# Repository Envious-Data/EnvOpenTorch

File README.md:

# EnvOpenTorch
 A open source rechargable LED Torch

## Notes
This design is a bit jank and can certaily do with some improvement, If you feel like doing that then please do so and make a PR.

Generally speaking is to have a decently powerful open source LED torch, Im hoping for 10K lumens and some basic brightness control, anything else is bonnus features but there are some i'd like such as PD charging and being able to act as a battery bank if needed.

## Future plans
Im probably going to sell this as a full unit or kit other than the need to supply your own cells, I havent decided on 3S2P or 6S1P but for the time being the charge circuit can handle upto 4S.

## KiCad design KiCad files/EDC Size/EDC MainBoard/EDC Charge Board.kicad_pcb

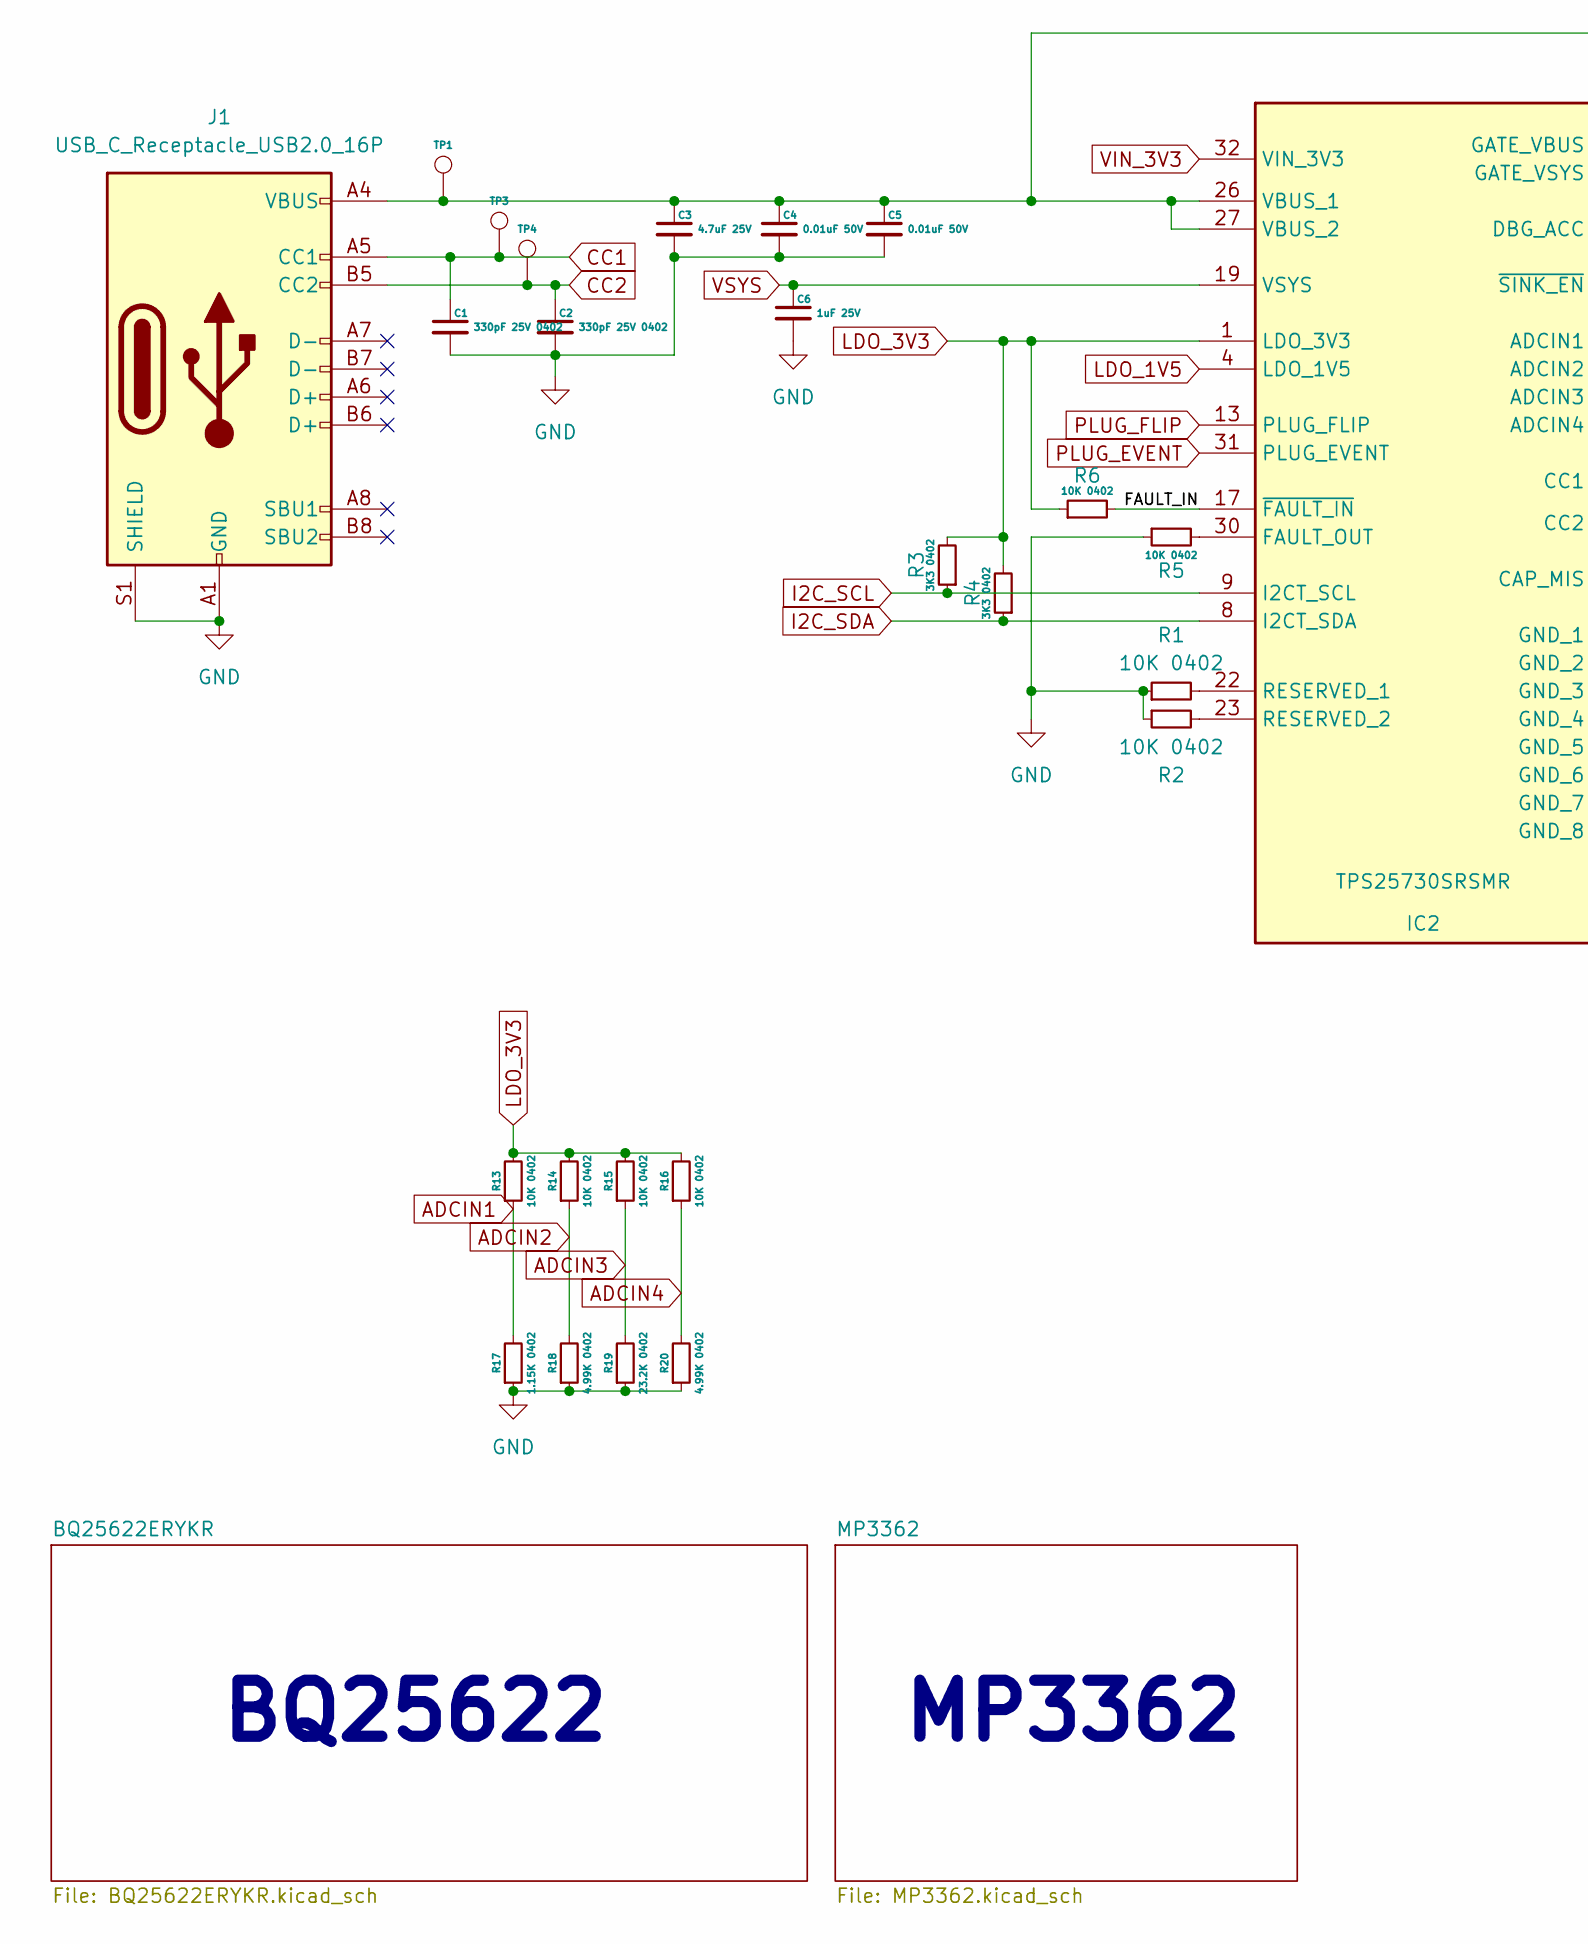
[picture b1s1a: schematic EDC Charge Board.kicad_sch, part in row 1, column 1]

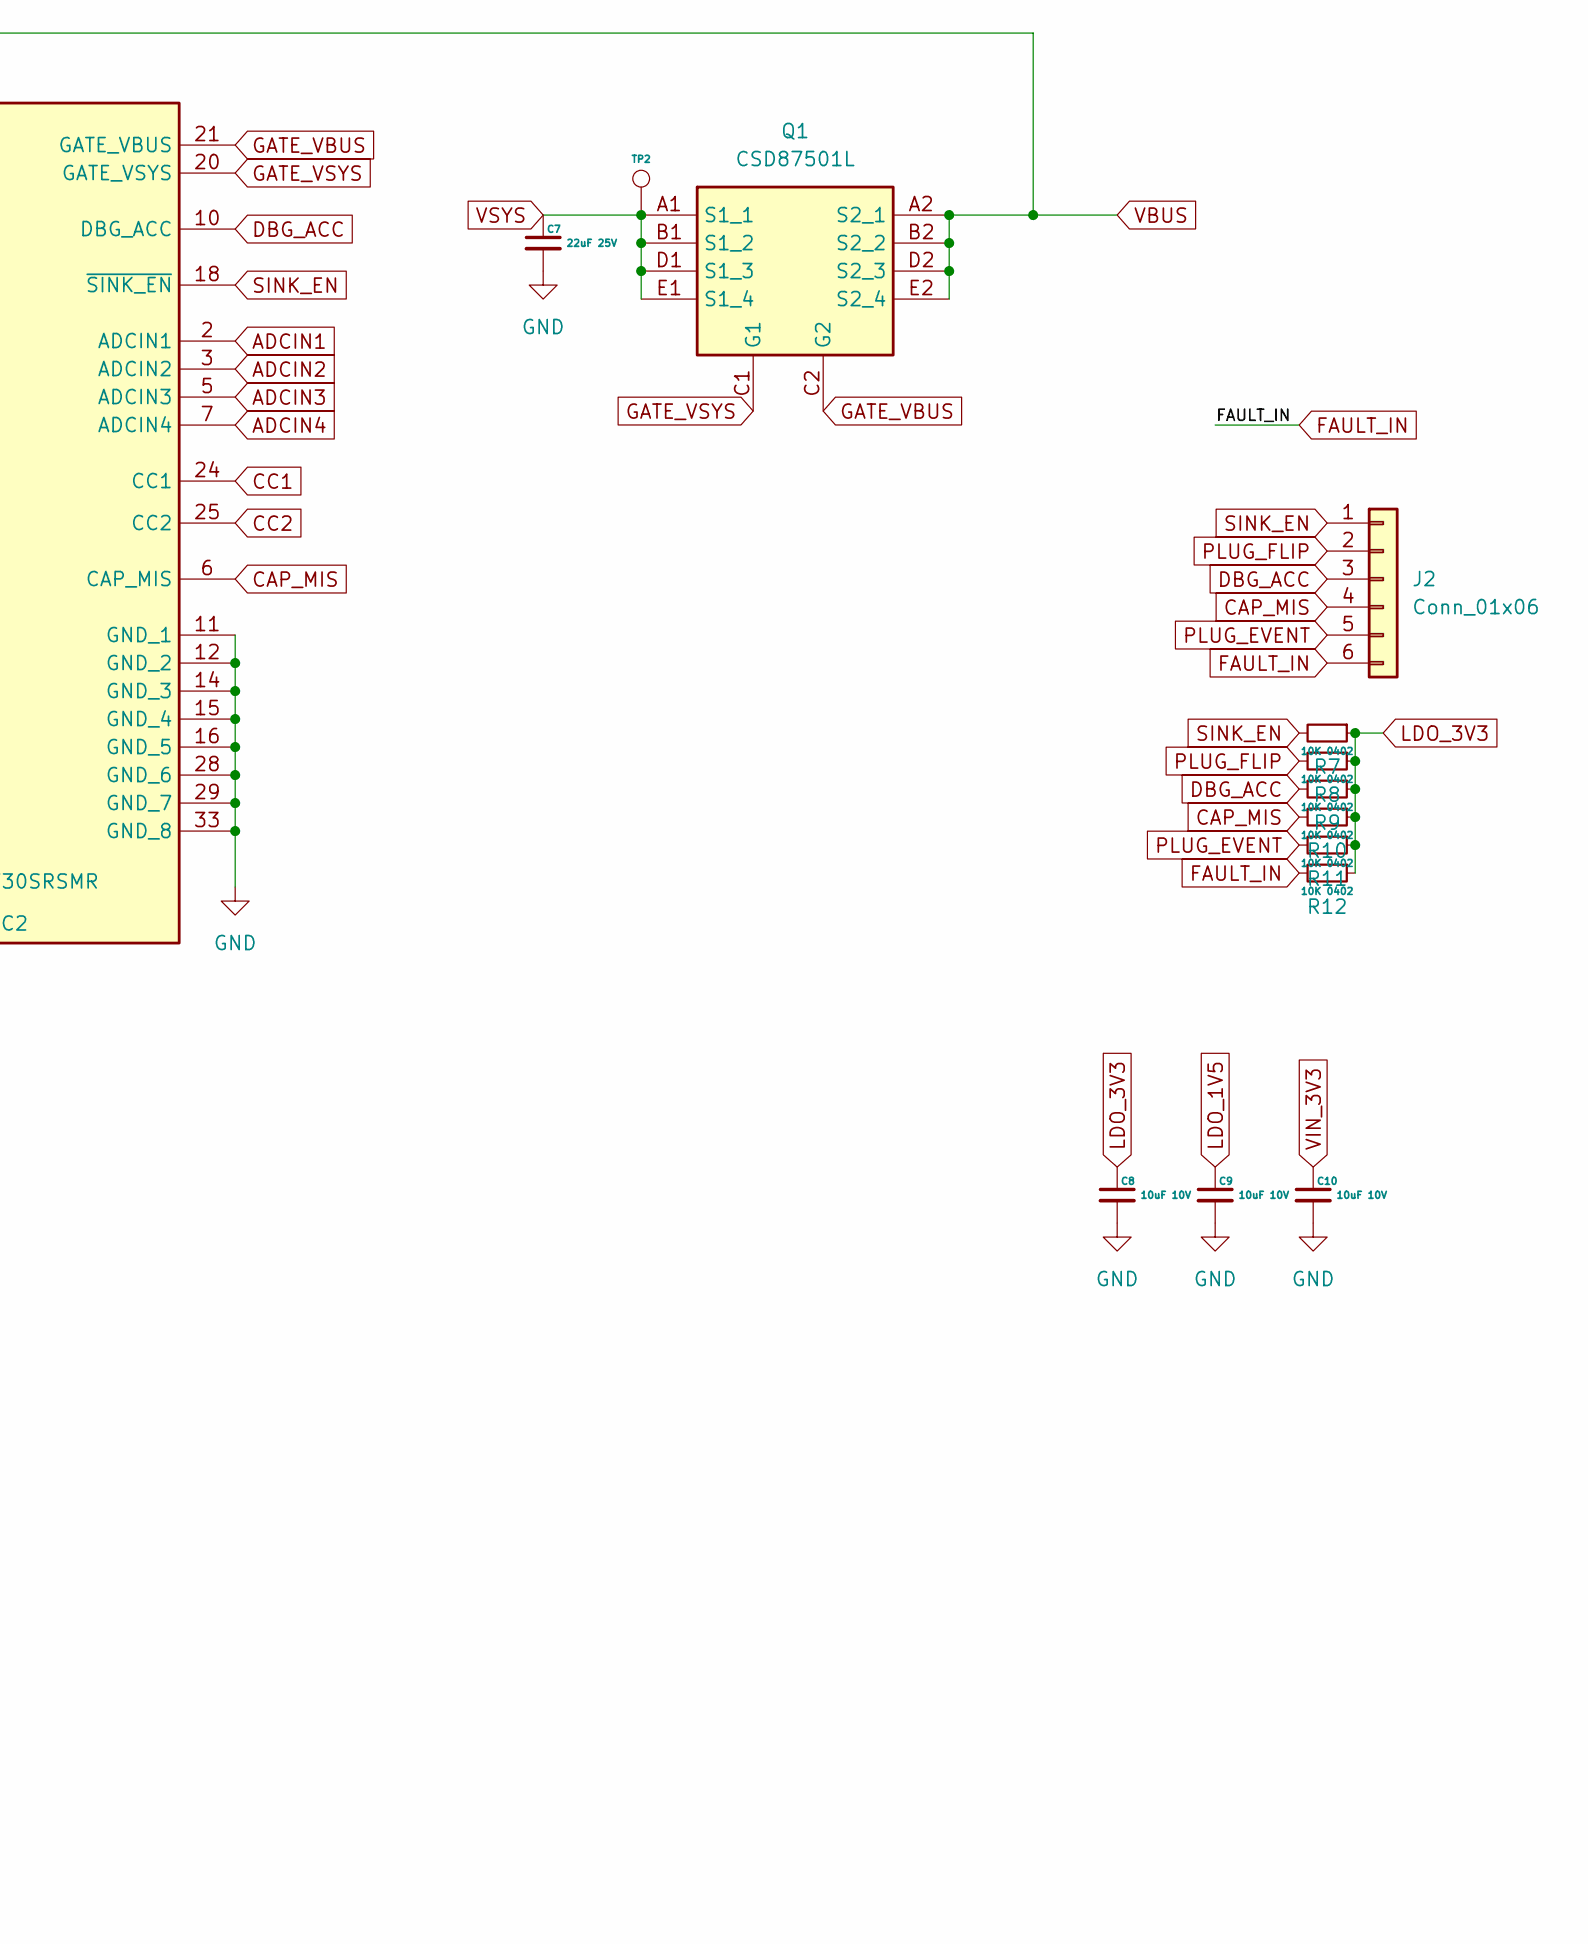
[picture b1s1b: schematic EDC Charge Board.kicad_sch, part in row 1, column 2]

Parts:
C1, C2: 330pF 25V 0402; C_0402_1005Metric
C3: 4.7uF 25V; C_0402_1005Metric
C4, C5: 0.01uF 50V; C_0402_1005Metric
C6: 1uF 25V; C_0402_1005Metric
C7: 22uF 25V; C_0402_1005Metric
C8, C9, C10: 10uF 10V; C_0402_1005Metric
IC2: TPS25730SRSMR; QFN40P400X400X100-33N-D; Mouser Part Number 595-TPS25730SRSMR
J1: USB_C_Receptacle_USB2.0_16P; USB_C_Receptacle_HRO_TYPE-C-31-M-12
J2: Conn_01x06; PinHeader_1x06_P2.54mm_Vertical
Q1: CSD87501L; Mouser Part Number 595-CSD87501L
R1, R2, R5, R6, R7, R8, R9, R10, R11, R12, R13, R14, R15, R16: 10K 0402; R_0402_1005Metric
R3, R4: 3K3 0402; R_0402_1005Metric
R17: 1.15K 0402; R_0402_1005Metric
R18, R20: 4.99K 0402; R_0402_1005Metric
R19: 23.2K 0402; R_0402_1005Metric
TP1, TP2, TP3, TP4: TestPoint; TestPoint_Pad_D1.0mm

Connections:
ADCIN1: IC2.2 (ADCIN1), R13.1, R17.2
ADCIN2: IC2.3 (ADCIN2), R14.1, R18.2
ADCIN3: IC2.5 (ADCIN3), R15.1, R19.2
ADCIN4: IC2.7 (ADCIN4), R16.1, R20.2
CAP_MIS: IC2.6 (CAP_MIS), J2.4, R10.2
CC1: C1.1, IC2.24 (CC1), J1.A5 (CC1), TP3.1
CC2: C2.1, IC2.25 (CC2), J1.B5 (CC2), TP4.1
DBG_ACC: IC2.10 (DBG_ACC), J2.3, R9.2
FAULT_IN: IC2.17 (~FAULT_IN), J2.6, R6.2, R12.2
GATE_VBUS: IC2.21 (GATE_VBUS), Q1.C2 (G2)
GATE_VSYS: IC2.20 (GATE_VSYS), Q1.C1 (G1)
GND: C1.2, C2.2, C3.2, C4.2, C5.2, C6.2, C7.2, C8.2, C9.2, C10.2, IC2.11 (GND_1), IC2.12 (GND_2), IC2.14 (GND_3), IC2.15 (GND_4), IC2.16 (GND_5), IC2.28 (GND_6), IC2.29 (GND_7), IC2.33 (GND_8), J1.A1 (GND), J1.A12 (GND), J1.B1 (GND), J1.B12 (GND), J1.S1 (SHIELD), R1.1, R2.1, R5.1, R17.1, R18.1, R19.1, R20.1; also elsewhere on the board
I2C_SCL: IC2.9 (I2CT_SCL), R3.1; also elsewhere on the board
I2C_SDA: IC2.8 (I2CT_SDA), R4.1; also elsewhere on the board
LDO_1V5: C9.1, IC2.4 (LDO_1V5)
LDO_3V3: C8.1, IC2.1 (LDO_3V3), R3.2, R4.2, R6.1, R7.1, R8.1, R9.1, R10.1, R11.1, R12.1, R13.2, R14.2, R15.2, R16.2
unnamed: IC2.30 (FAULT_OUT), R5.2
unnamed: IC2.22 (RESERVED_1), R1.2
unnamed: IC2.23 (RESERVED_2), R2.2
PLUG_EVENT: IC2.31 (PLUG_EVENT), J2.5, R11.2
PLUG_FLIP: IC2.13 (PLUG_FLIP), J2.2, R8.2
SINK_EN: IC2.18 (~SINK_EN), J2.1, R7.2
VBUS: C3.1, C4.1, C5.1, IC2.26 (VBUS_1), IC2.27 (VBUS_2), J1.A4 (VBUS), J1.A9 (VBUS), J1.B4 (VBUS), J1.B9 (VBUS), Q1.A2 (S2_1), Q1.B2 (S2_2), Q1.D2 (S2_3), Q1.E2 (S2_4), TP1.1
VIN_3V3: C10.1, IC2.32 (VIN_3V3)
VSYS: C6.1, C7.1, IC2.19 (VSYS), Q1.A1 (S1_1), Q1.B1 (S1_2), Q1.D1 (S1_3), Q1.E1 (S1_4), TP2.1; also elsewhere on the board

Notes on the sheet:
MP3362
BQ25622

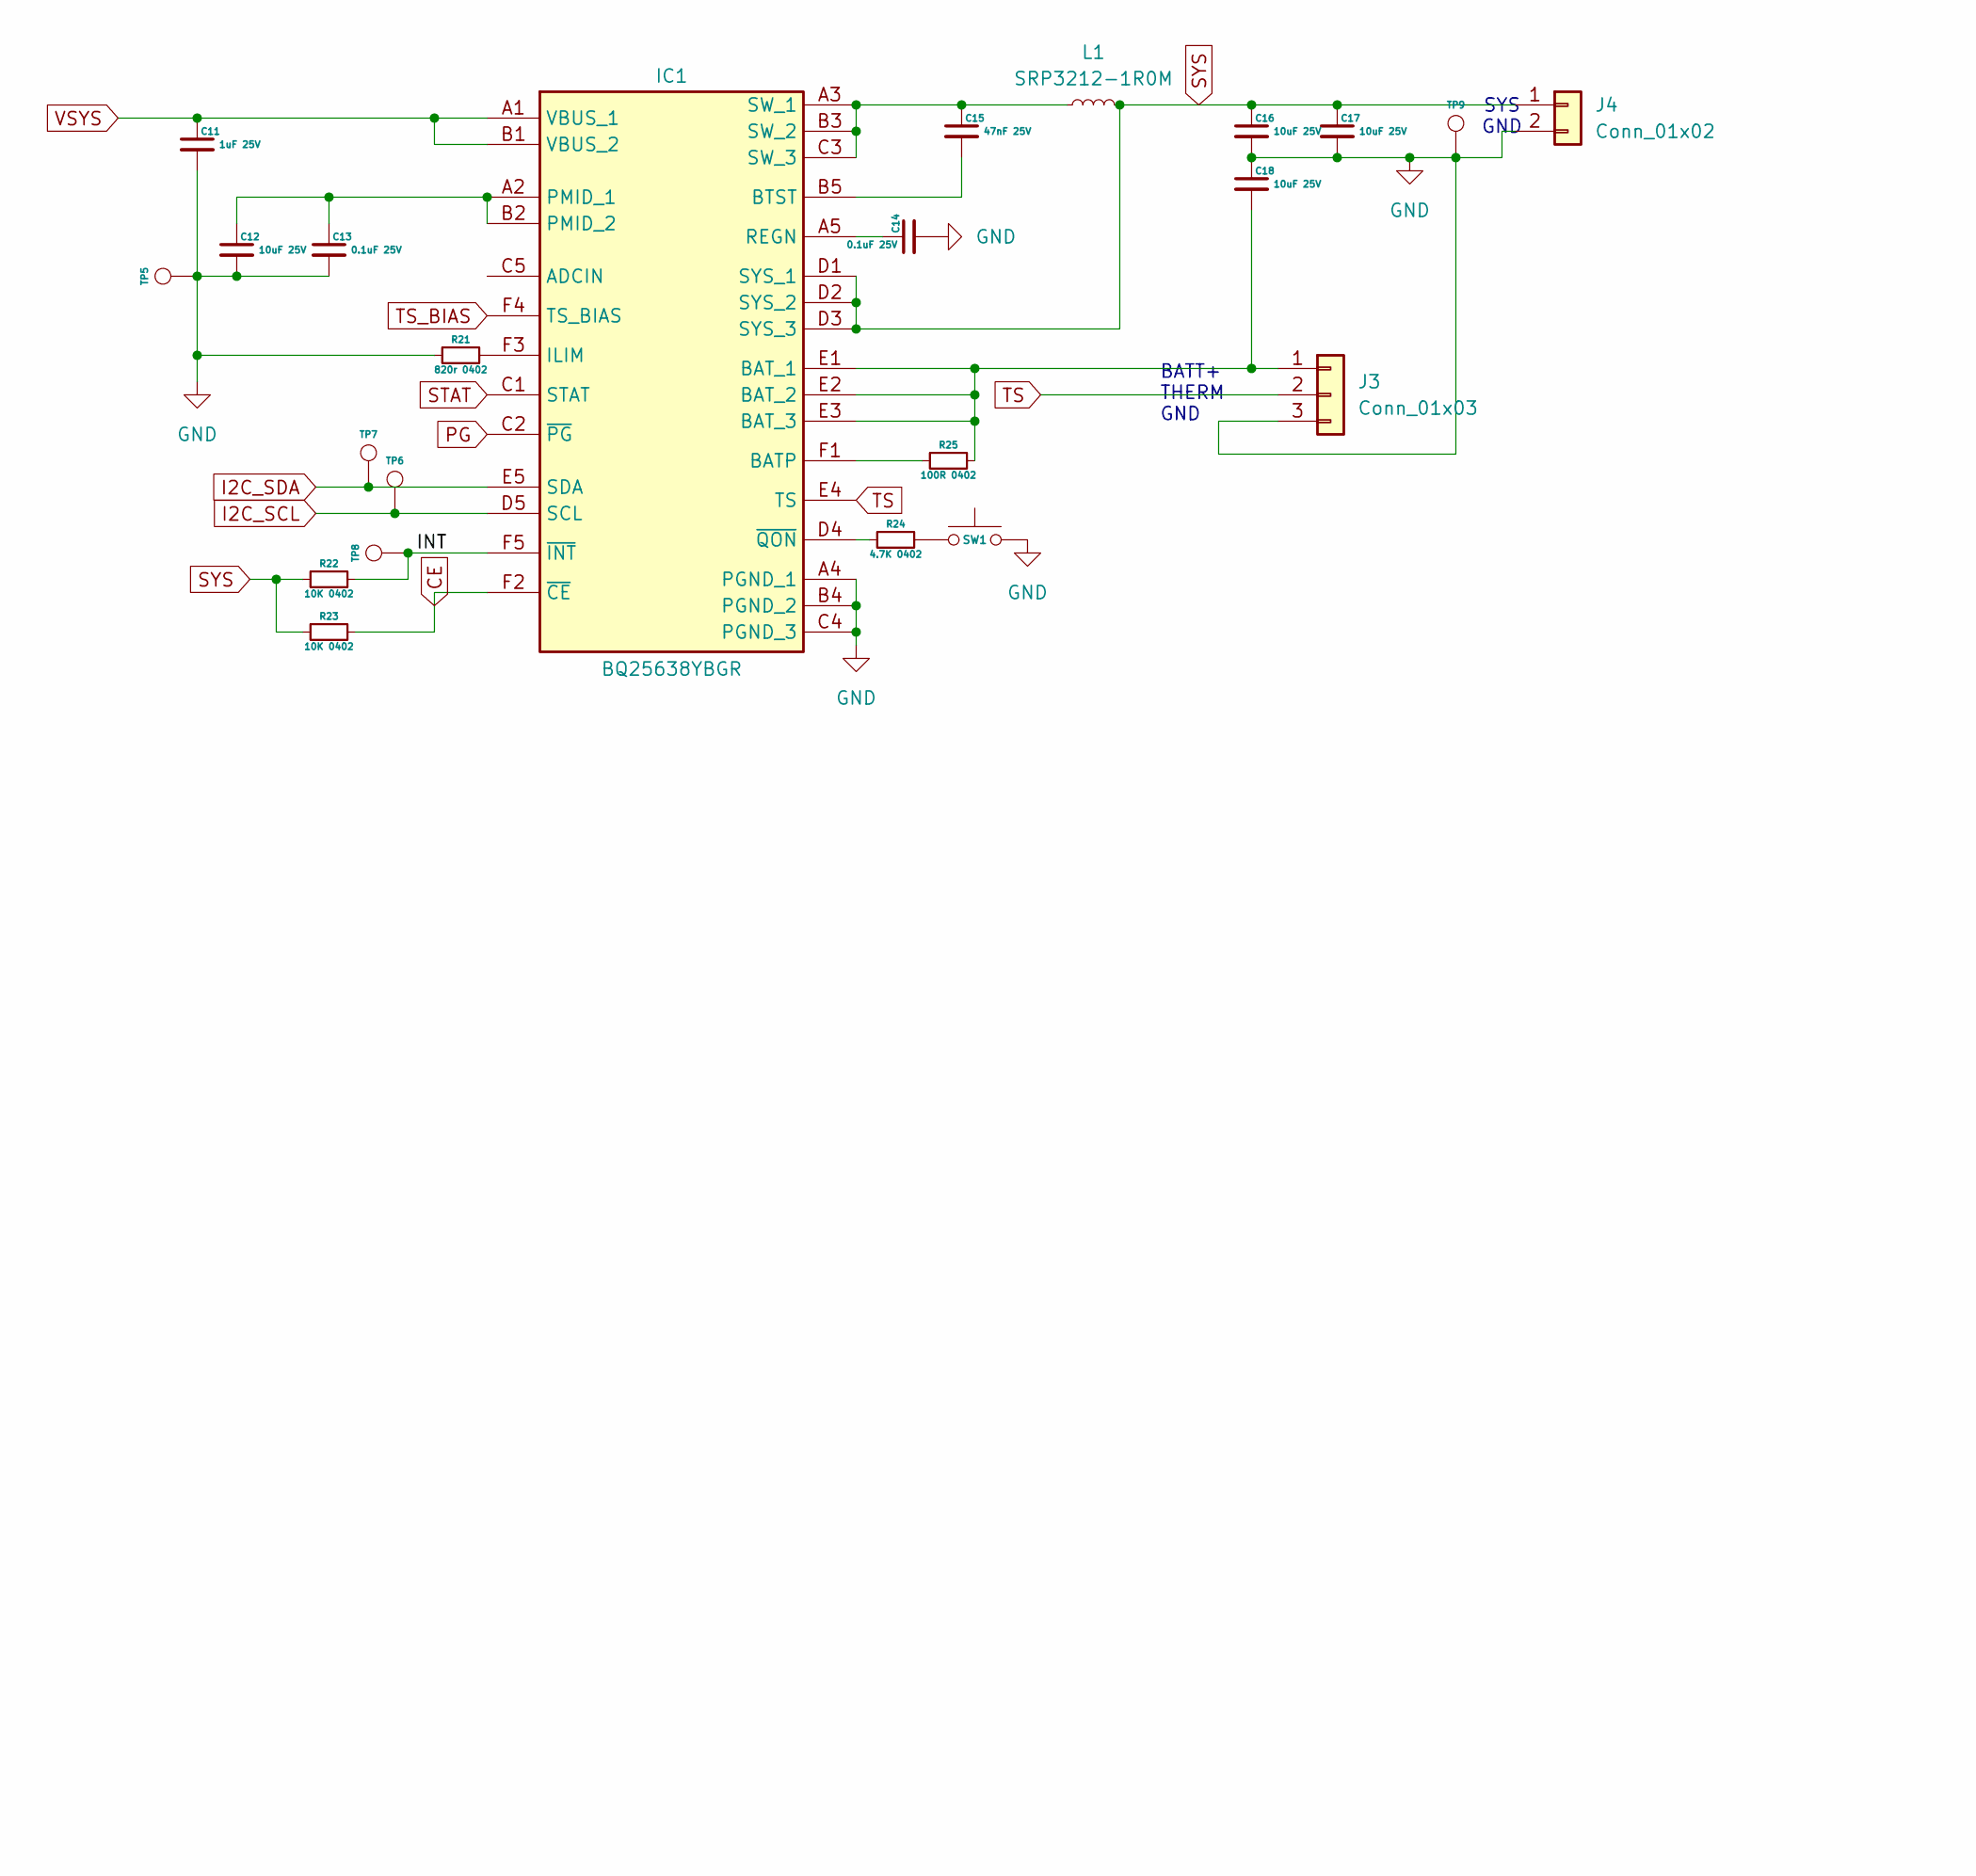
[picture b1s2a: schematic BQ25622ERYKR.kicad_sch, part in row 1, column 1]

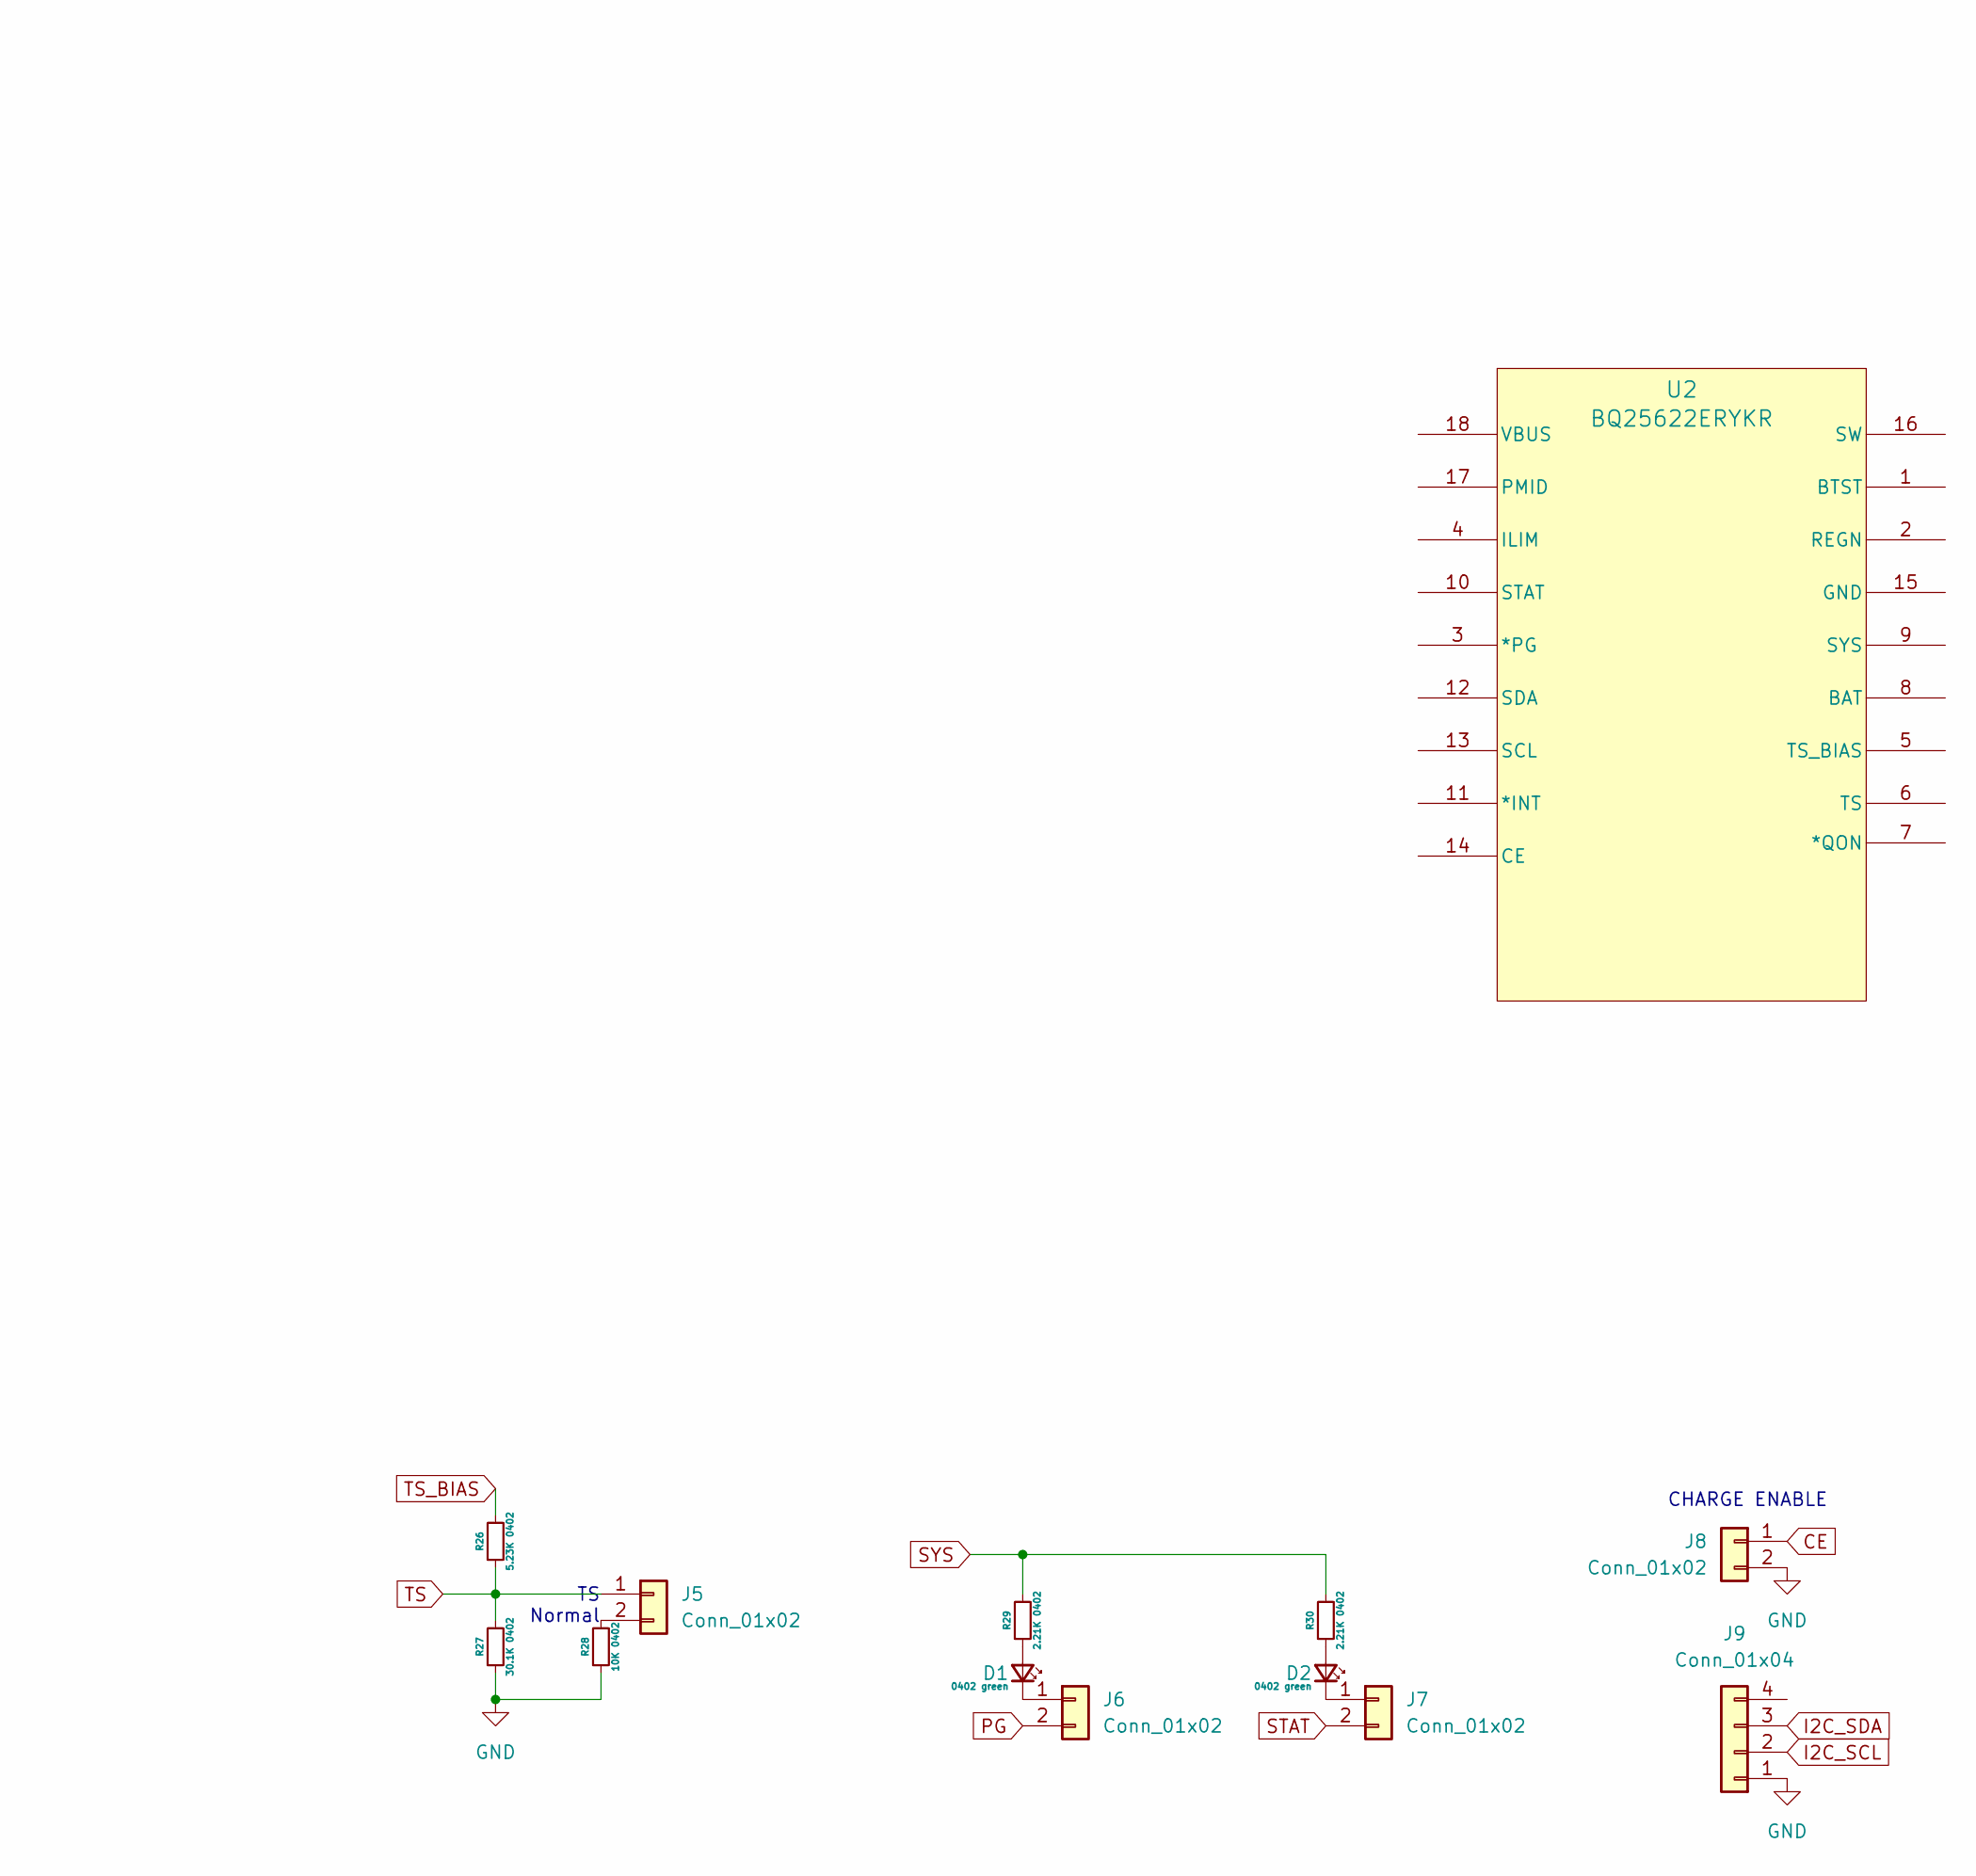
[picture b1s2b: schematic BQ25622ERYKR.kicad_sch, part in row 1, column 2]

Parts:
C11: 1uF 25V; C_0402_1005Metric
C12, C16, C17, C18: 10uF 25V; C_0402_1005Metric
C13, C14: 0.1uF 25V; C_0402_1005Metric
C15: 47nF 25V; C_0402_1005Metric
D1, D2: 0402 green; LED_0402_1005Metric
IC1: BQ25638YBGR; BGA30C40P5X6_227X198X50; Mouser Part Number 595-BQ25638YBGR
J3: Conn_01x03; PinHeader_1x03_P2.54mm_Vertical
J4: Conn_01x02; PinHeader_1x02_P2.54mm_Vertical
J5, J6, J7: Conn_01x02; SolderJumper-2_P1.3mm_Open_RoundedPad1.0x1.5mm
J8: Conn_01x02; SolderJumper-2_P1.3mm_Bridged_RoundedPad1.0x1.5mm
J9: Conn_01x04; PinSocket_1x04_P2.54mm_Vertical
L1: SRP3212-1R0M; L_Wurth_WE-LQSH-3012
R21: 820r 0402; R_0402_1005Metric
R22, R23, R28: 10K 0402; R_0402_1005Metric
R24: 4.7K 0402; R_0402_1005Metric
R25: 100R 0402; R_0402_1005Metric
R26: 5.23K 0402; R_0402_1005Metric
R27: 30.1K 0402; R_0402_1005Metric
R29, R30: 2.21K 0402; R_0402_1005Metric
SW1: SW_Push; SW_SPST_B3U-1000P
TP5, TP6, TP7, TP8, TP9: TestPoint; TestPoint_Pad_D1.0mm
U2: BQ25622ERYKR; WQFN-HR18_RYK_TEX

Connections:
/BQ25638/INT: IC1.F5 (~INT), R22.2, TP8.1
CE: IC1.F2 (~CE), J8.1, R23.2
GND: C11.2, C12.2, C13.2, C14.2, C16.2, C17.2, C18.1, IC1.A4 (PGND_1), IC1.B4 (PGND_2), IC1.C4 (PGND_3), J3.3, J4.2, J8.2, J9.1, R21.1, R27.1, R28.1, SW1.2, TP5.1, TP9.1; also elsewhere on the board
I2C_SCL: IC1.D5 (SCL), J9.2, TP6.1; also elsewhere on the board
I2C_SDA: IC1.E5 (SDA), J9.3, TP7.1; also elsewhere on the board
unnamed: D1.2 (A), R29.1
unnamed: D1.1 (K), J6.1
unnamed: D2.2 (A), R30.1
unnamed: D2.1 (K), J7.1
unnamed: IC1.F1 (BATP), R25.1
unnamed: C18.2, IC1.E1 (BAT_1), IC1.E2 (BAT_2), IC1.E3 (BAT_3), J3.1, R25.2
unnamed: C15.2, IC1.B5 (BTST)
unnamed: IC1.F3 (ILIM), R21.2
unnamed: C12.1, C13.1, IC1.A2 (PMID_1), IC1.B2 (PMID_2)
unnamed: C14.1, IC1.A5 (REGN)
unnamed: C15.1, IC1.A3 (SW_1), IC1.B3 (SW_2), IC1.C3 (SW_3), L1.1
unnamed: IC1.D4 (~QON), R24.1
unnamed: J5.2, R28.2
unnamed: R24.2, SW1.1
PG: IC1.C2 (~PG), J6.2
STAT: IC1.C1 (STAT), J7.2
SYS: C16.1, C17.1, IC1.D1 (SYS_1), IC1.D2 (SYS_2), IC1.D3 (SYS_3), J4.1, L1.2, R22.1, R23.1, R29.2, R30.2; also elsewhere on the board
TS: IC1.E4 (TS), J3.2, J5.1, R26.1, R27.2
TS_BIAS: IC1.F4 (TS_BIAS), R26.2
VSYS: C11.1, IC1.A1 (VBUS_1), IC1.B1 (VBUS_2); also elsewhere on the board

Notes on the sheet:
CHARGE ENABLE
TS Normal
BATT+ THERM GND
SYS GND

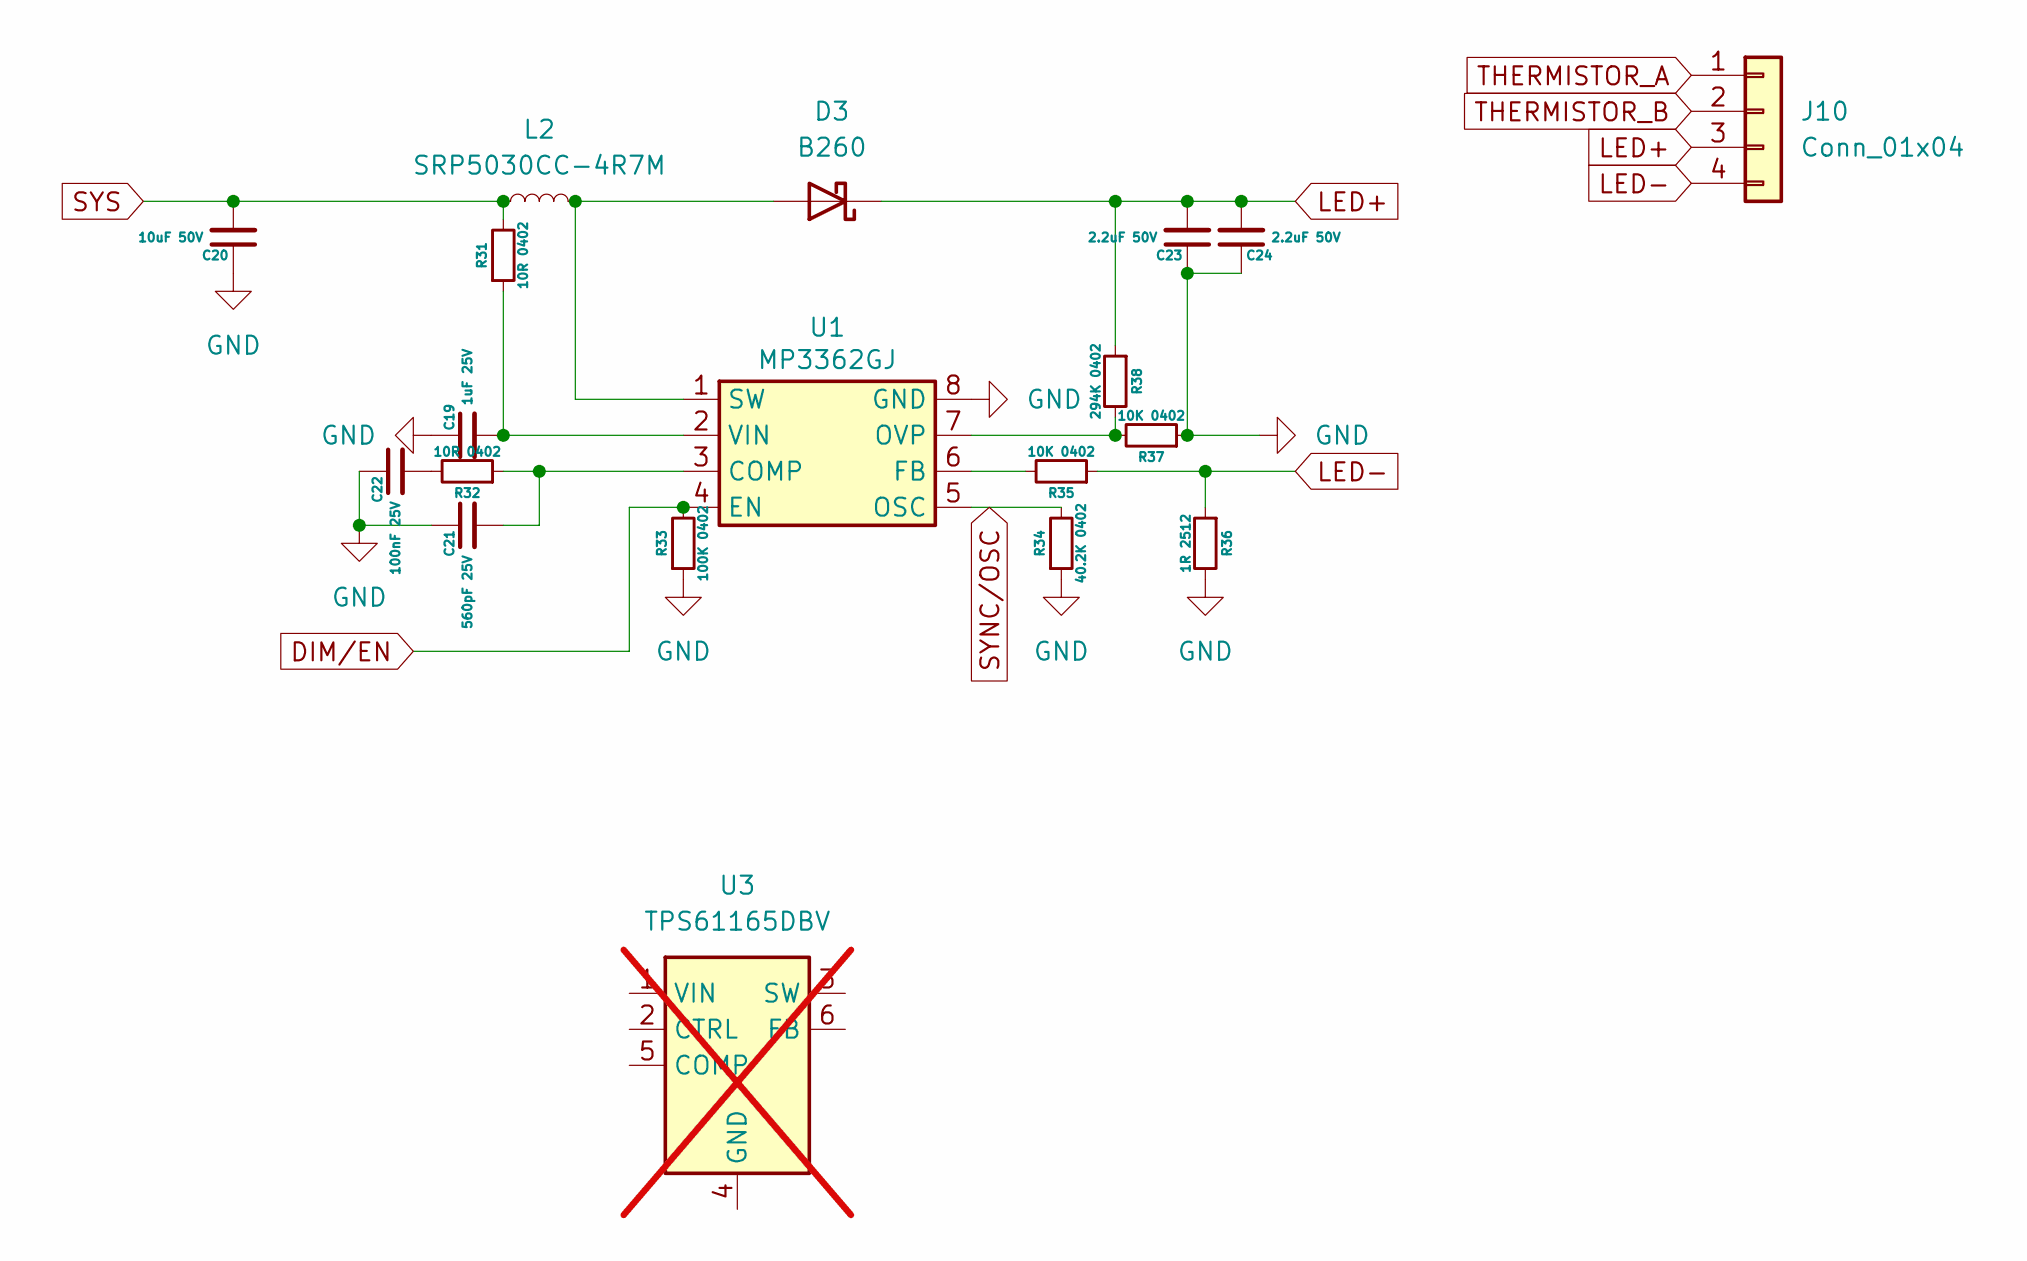
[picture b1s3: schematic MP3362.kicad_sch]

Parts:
C19: 1uF 25V; C_0402_1005Metric
C20: 10uF 50V; C_0402_1005Metric
C21: 560pF 25V; C_0402_1005Metric
C22: 100nF 25V; C_0402_1005Metric
C23, C24: 2.2uF 50V; C_0402_1005Metric
D3: B260; D_SMB
J10: Conn_01x04; PinSocket_1x04_P2.54mm_Vertical
L2: SRP5030CC-4R7M; L_Bourns_SRP5030T
R31, R32: 10R 0402; R_0402_1005Metric
R33: 100K 0402; R_0402_1005Metric
R34: 40.2K 0402; R_0402_1005Metric
R35, R37: 10K 0402; R_0402_1005Metric
R36: 1R 2512; R_2512_6332Metric
R38: 294K 0402; R_0402_1005Metric
U1: MP3362GJ; TSOT-23-8
U3: TPS61165DBV; SOT-23-6_Handsoldering; not fitted

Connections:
DIM/EN: R33.2, U1.4 (EN)
GND: C19.1, C20.1, C21.1, C22.1, C23.1, C24.1, R33.1, R34.1, R36.2, R37.1, U1.8 (GND); also elsewhere on the board
LED+: C23.2, C24.2, D3.1 (K), J10.3, R38.1
LED-: J10.4, R35.1, R36.1
unnamed: C22.2, R32.2
unnamed: D3.2 (A), L2.2, U1.1 (SW)
unnamed: C21.2, R32.1, U1.3 (COMP)
unnamed: R35.2, U1.6 (FB)
unnamed: R37.2, R38.2, U1.7 (OVP)
unnamed: C19.2, R31.1, U1.2 (VIN)
SYNC/OSC: R34.2, U1.5 (OSC)
SYS: C20.2, L2.1, R31.2; also elsewhere on the board
THERMISTOR_A: J10.1
THERMISTOR_B: J10.2

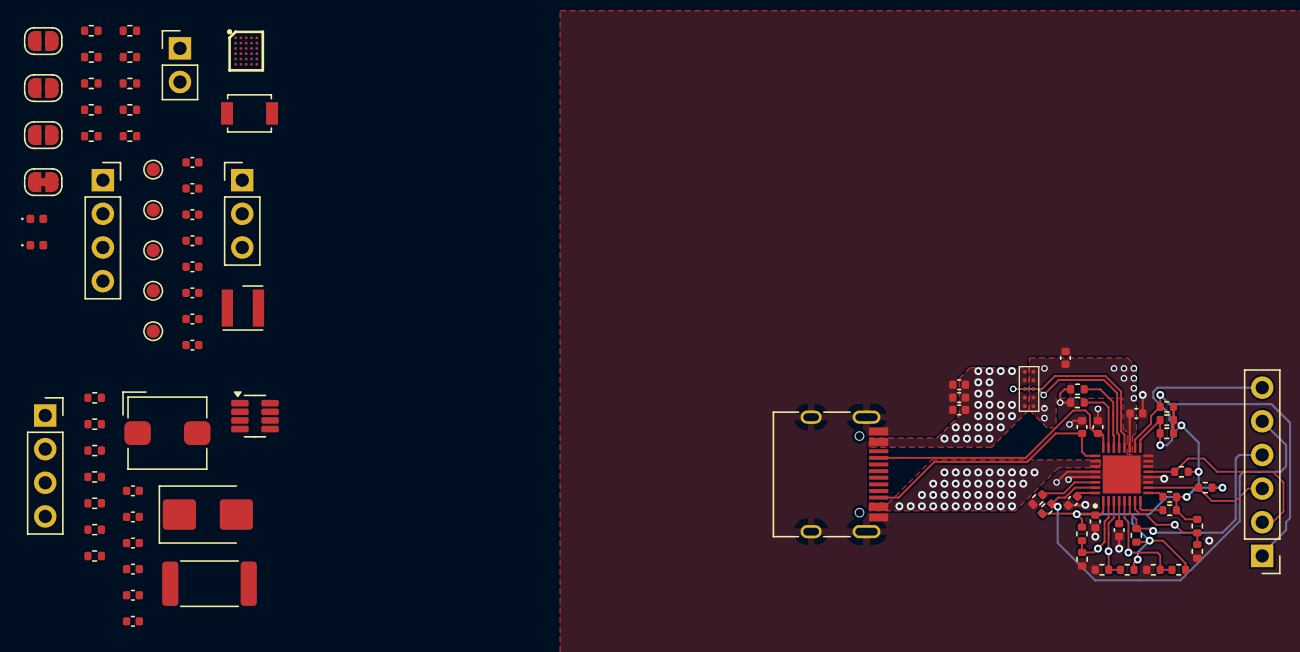
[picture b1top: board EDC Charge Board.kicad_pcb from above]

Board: 2 copper layers, 87 parts (0 on the bottom side), 56 nets.
